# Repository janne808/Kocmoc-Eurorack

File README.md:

# Kocmoc-Eurorack

Copyright (c) 2021 Janne Heikkarainen (janne808@radiofreerobotron.net)

All rights reserved.

### Kocmoc Free Open Source Hardware for Eurorack

* SVF

   Voltage controlled state variable filter design based on the VCV Rack module of the same name. PCB Eurorack compatible panel included.

   Files are made for Eagle 9.x

# Licence

All hardware descriptions, board designs and schematics are released under CERN Open Hardware Licence Version 2 - Strongly Reciprocal, please find the full text as part of this repo

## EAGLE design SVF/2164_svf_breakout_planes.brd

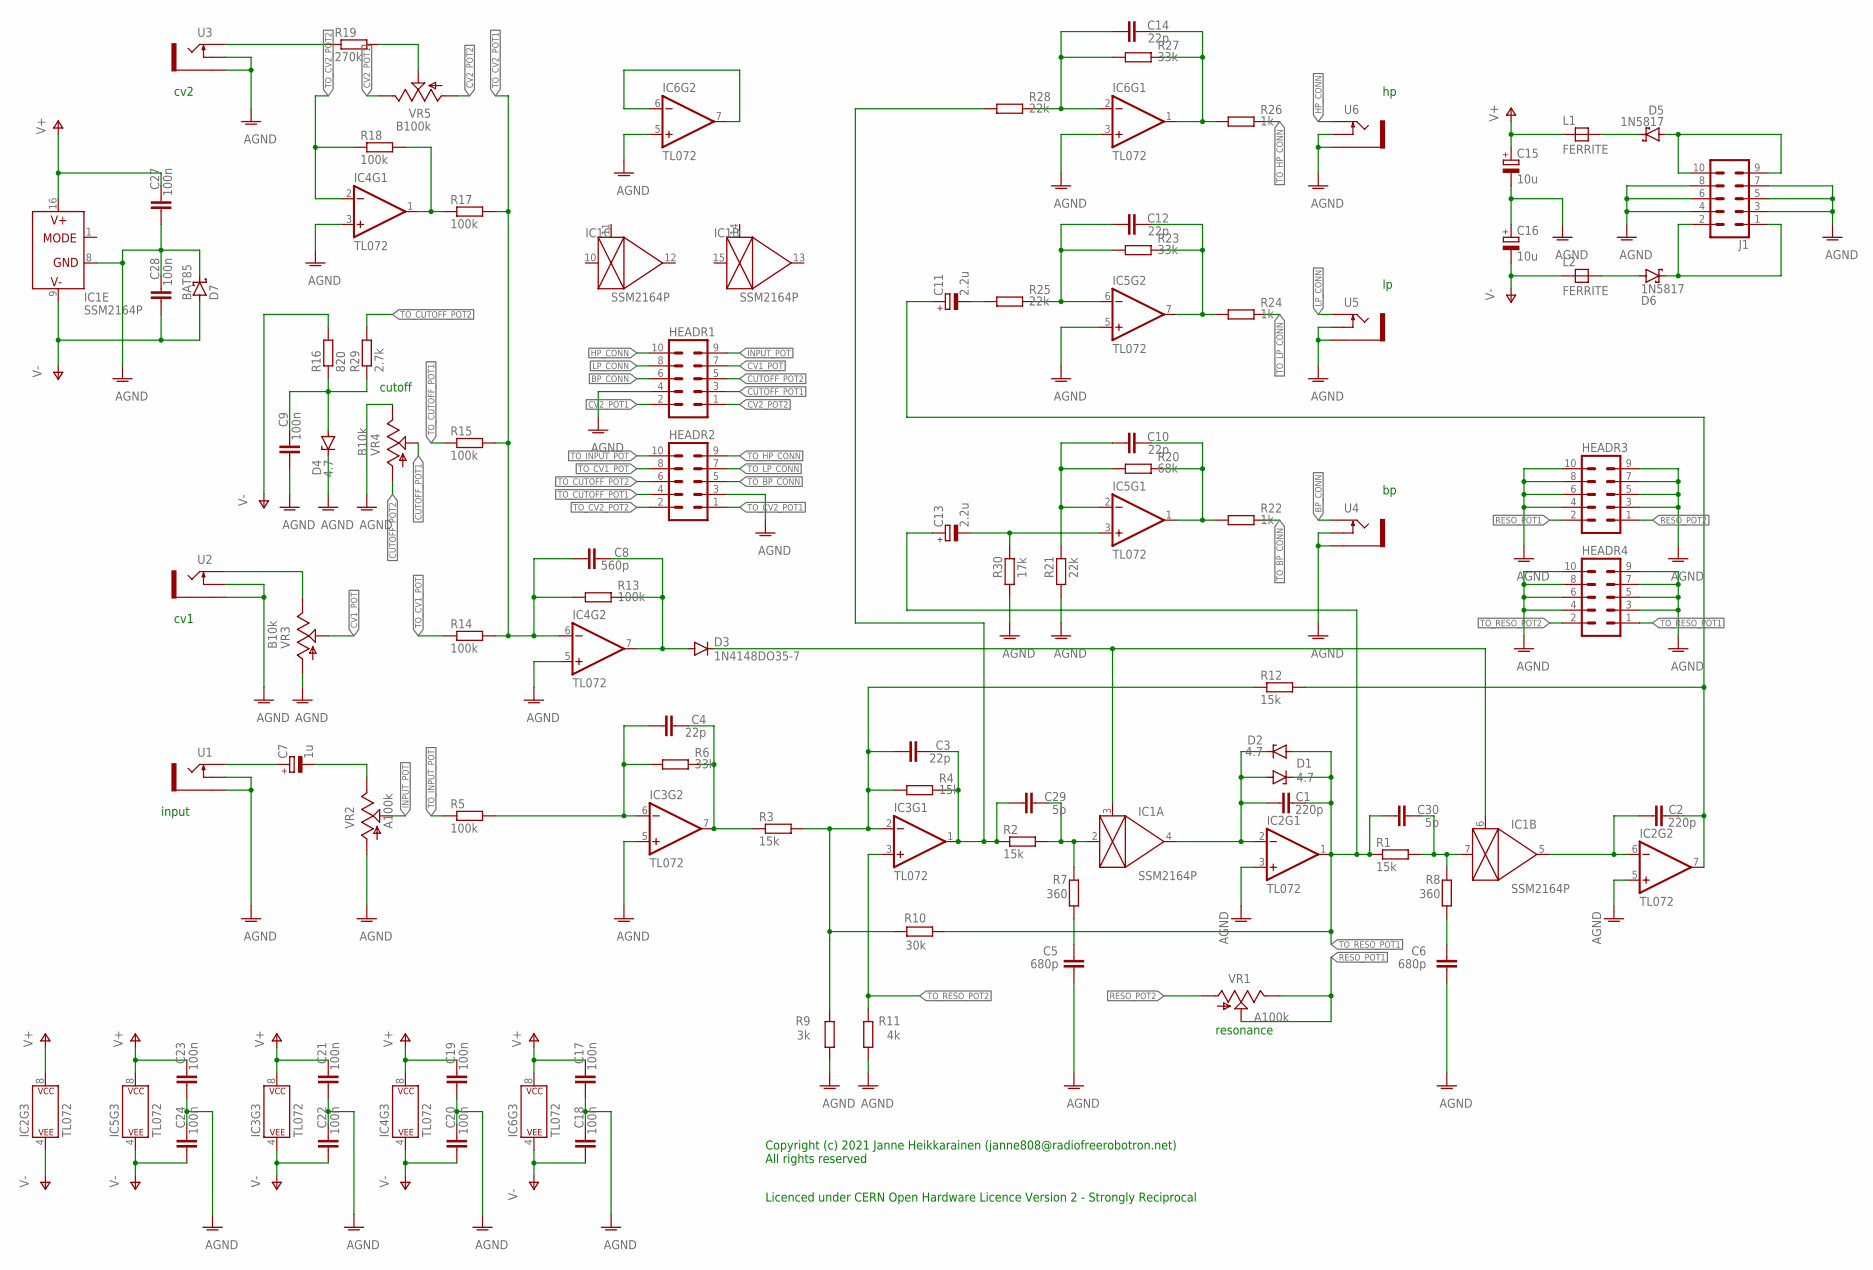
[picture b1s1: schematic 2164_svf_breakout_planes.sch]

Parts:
C1, C2: 220p; C050-025X075
C3, C4, C10, C12, C14: 22p; C050-025X075
C5, C6: 680p; C050-025X075
C7: 1u; E2,5-6E
C8: 560p; C050-025X075
C9, C17, C18, C19, C20, C21, C22, C23, C24, C27, C28: 100n; C050-025X075
C11, C13: 2.2u; E2,5-6E
C15, C16: 10u; E2,5-6E
C29, C30: 5p; C050-025X075
D1, D2, D4: 4.7; DO34Z7
D3: 1N4148DO35-7; DO35-7
D5, D6: 1N5817; DO35-7
D7: BAT85; DO35-7
HEADR1, HEADR2, HEADR3, HEADR4: 10PIN_BACKSIDE
IC1: SSM2164P; DIL16
IC2, IC3, IC4, IC5, IC6: TL072; DIP08
J1: CONN_05X2SHD; 2X5-SHROUDED
L1, L2: FERRITE; FB-085
R1, R2, R3, R4, R12: 15k; 0207/2V
R5, R13, R14, R15, R17, R18: 100k; 0207/2V
R6, R23, R27: 33k; 0207/2V
R7, R8: 360; 0207/2V
R9: 3k; 0207/2V
R10: 30k; 0207/2V
R11: 4k; 0207/2V
R16: 820; 0207/2V
R19: 270k; 0207/2V
R20: 68k; 0207/2V
R21, R25, R28: 22k; 0207/2V
R22, R24, R26: 1k; 0207/2V
R29: 2.7k; 0207/2V
R30: 17k; 0207/2V
U1, U2, U3, U4, U5, U6: THONKICONNNEW; WQP-PJ301M-12_JACK
VR1, VR2: A100k; 9MM_SNAP-IN_POT
VR3, VR4: B10k; 9MM_SNAP-IN_POT
VR5: B100k; 9MM_SNAP-IN_POT

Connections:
AGND: C5.1, C6.1, C9.1, C15.-, C16.+, C17.1, C18.2, C19.1, C20.2, C21.1, C22.2, C23.1, C24.2, C27.1, C28.2, D4.C, D7.C, HEADR1.4, HEADR2.3, HEADR3.3, HEADR3.4, HEADR3.5, HEADR3.6, HEADR3.7, HEADR3.8, HEADR3.9, HEADR3.10, HEADR4.3, HEADR4.4, HEADR4.5, HEADR4.6, HEADR4.7, HEADR4.8, HEADR4.9, HEADR4.10, IC1.8 (GND), IC2.3 (+IN), IC2.5 (+IN), IC3.5 (+IN), IC4.3 (+IN), IC4.5 (+IN), IC5.5 (+IN), IC6.3 (+IN), IC6.5 (+IN), J1.3, J1.4, J1.5, J1.6, J1.7, J1.8, R9.1, R11.1, R21.1, R30.1, U1.P$2_SWITCH (SWITCH), U1.P$3_SLEEVE (SLEEVE), U2.P$2_SWITCH (SWITCH), U2.P$3_SLEEVE (SLEEVE), U3.P$2_SWITCH (SWITCH), U3.P$3_SLEEVE (SLEEVE), U4.P$2_SWITCH (SWITCH), U4.P$3_SLEEVE (SLEEVE), U5.P$2_SWITCH (SWITCH), U5.P$3_SLEEVE (SLEEVE), U6.P$2_SWITCH (SWITCH), U6.P$3_SLEEVE (SLEEVE), VR2.1 (A), VR3.1 (A), VR4.3 (E)
BP_CONN: HEADR1.6, U4.P$1_TIP (TIP)
CUTOFF_POT1: HEADR1.3, VR4.2 (S)
CUTOFF_POT2: HEADR1.5, VR4.1 (A)
CV1_POT: HEADR1.7, VR3.2 (S)
CV2_POT1: HEADR1.2, VR5.3 (E)
CV2_POT2: HEADR1.1, VR5.1 (A)
HP_CONN: HEADR1.10, U6.P$1_TIP (TIP)
INPUT_POT: HEADR1.9, VR2.2 (S)
LP_CONN: HEADR1.8, U5.P$1_TIP (TIP)
unnamed: C1.1, D1.A, D2.C, IC1.4 (OUT), IC2.2 (-IN)
unnamed: C2.1, IC1.5 (OUT), IC2.6 (-IN)
unnamed: C13.-, IC5.3 (+IN), R30.2
unnamed: C30.2, IC1.7 (IN), R1.2, R8.2
unnamed: C3.2, C29.1, IC3.1 (OUT), R2.1, R4.2, R28.1
unnamed: C29.2, IC1.2 (IN), R2.2, R7.2
unnamed: C9.2, D4.A, R16.1, R29.1
unnamed: C4.2, IC3.7 (OUT), R3.1, R6.2
unnamed: C3.1, IC3.2 (-IN), R3.2, R4.1, R9.2, R10.2, R12.1
unnamed: C4.1, IC3.6 (-IN), R5.2, R6.1
unnamed: C2.2, C11.+, IC2.7 (OUT), R12.2
unnamed: C7.-, VR2.3 (E)
unnamed: C7.+, U1.P$1_TIP (TIP)
unnamed: C5.2, R7.1
unnamed: C6.2, R8.1
unnamed: C8.2, D3.A, IC4.7 (OUT), R13.2
unnamed: D3.C, IC1.3 (CTRL), IC1.6 (CTRL)
unnamed: U2.P$1_TIP (TIP), VR3.3 (E)
unnamed: IC4.1 (OUT), R17.1, R18.2
unnamed: C10.1, IC5.2 (-IN), R20.1, R21.2
unnamed: R19.1, U3.P$1_TIP (TIP)
unnamed: R19.2, VR5.2 (S)
unnamed: C10.2, IC5.1 (OUT), R20.2, R22.1
unnamed: C12.1, IC5.6 (-IN), R23.1, R25.2
unnamed: C12.2, IC5.7 (OUT), R23.2, R24.1
unnamed: C11.-, R25.1
unnamed: IC6.6 (-IN), IC6.7 (OUT)
unnamed: D5.C, L1.2
unnamed: C14.2, IC6.1 (OUT), R26.1, R27.2
unnamed: C14.1, IC6.2 (-IN), R27.1, R28.2
unnamed: D6.A, L2.2
unnamed: D6.C, J1.1, J1.2
unnamed: D5.A, J1.9, J1.10
RESO_POT1: HEADR3.2, VR1.2 (S), VR1.3 (E)
RESO_POT2: HEADR3.1, VR1.1 (A)
TO_BP_CONN: HEADR2.5, R22.2
TO_CUTOFF_POT1: HEADR2.4, R15.1
TO_CUTOFF_POT2: HEADR2.6, R29.2
TO_CV1_POT: HEADR2.8, R14.1
TO_CV2_POT1: C8.1, HEADR2.1, IC4.6 (-IN), R13.1, R14.2, R15.2, R17.2
TO_CV2_POT2: HEADR2.2, IC4.2 (-IN), R18.1
TO_HP_CONN: HEADR2.9, R26.2
TO_INPUT_POT: HEADR2.10, R5.1
TO_LP_CONN: HEADR2.7, R24.2
TO_RESO_POT1: C1.2, C13.+, C30.1, D1.C, D2.A, HEADR4.1, IC2.1 (OUT), R1.1, R10.1
TO_RESO_POT2: HEADR4.2, IC3.3 (+IN), R11.2
V+: C15.+, C17.2, C19.2, C21.2, C23.2, C27.2, IC1.16 (V+), IC2.8 (P$V+), IC3.8 (P$V+), IC4.8 (P$V+), IC5.8 (P$V+), IC6.8 (P$V+), L1.1
V-: C16.-, C18.1, C20.1, C22.1, C24.1, C28.1, D7.A, IC1.9 (V-), IC2.4 (P$V-), IC3.4 (P$V-), IC4.4 (P$V-), IC5.4 (P$V-), IC6.4 (P$V-), L2.1, R16.2

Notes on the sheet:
resonance
cutoff
input
cv1
cv2
Copyright (c) 2021 Janne Heikkarainen (janne808@radiofreerobotron.net) All rights reserved
Licenced under CERN Open Hardware Licence Version 2 - Strongly Reciprocal

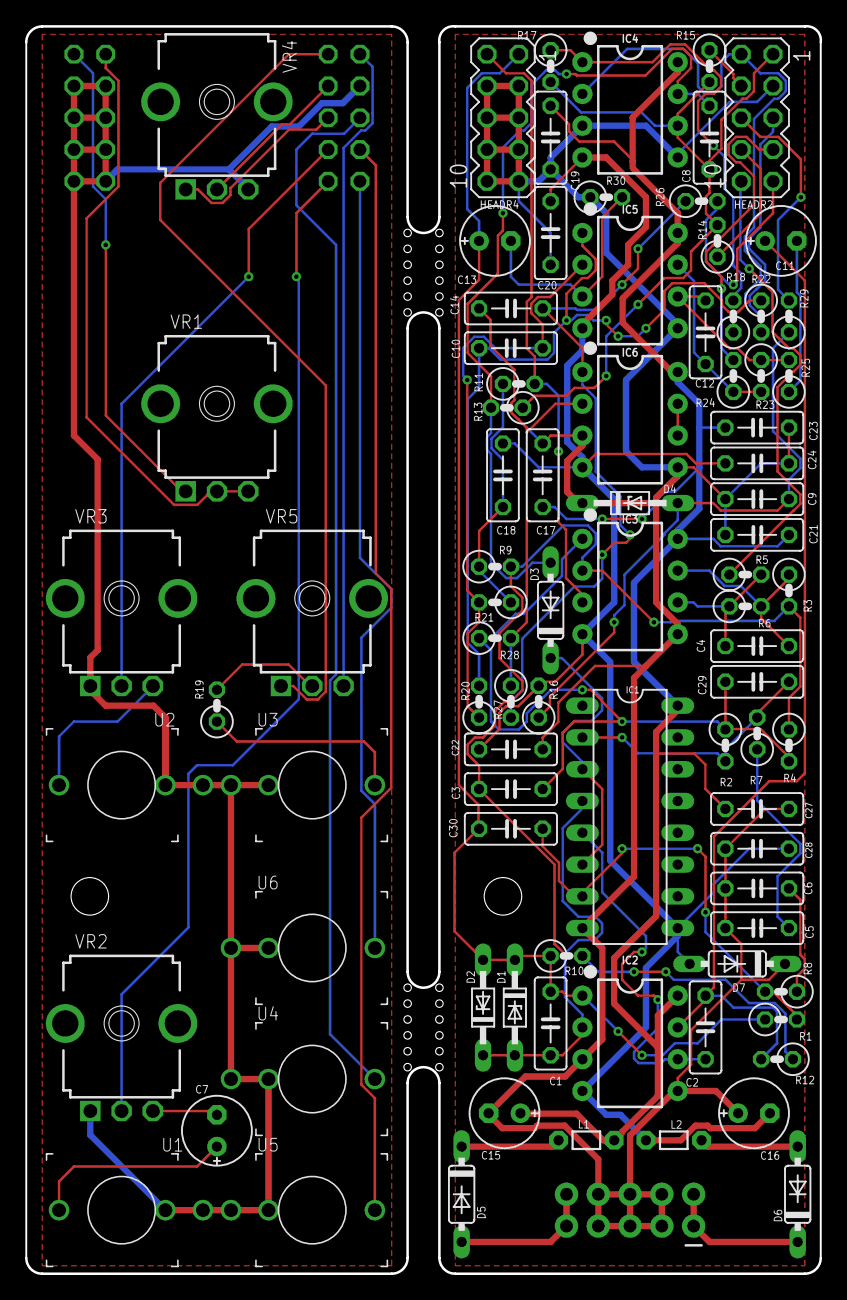
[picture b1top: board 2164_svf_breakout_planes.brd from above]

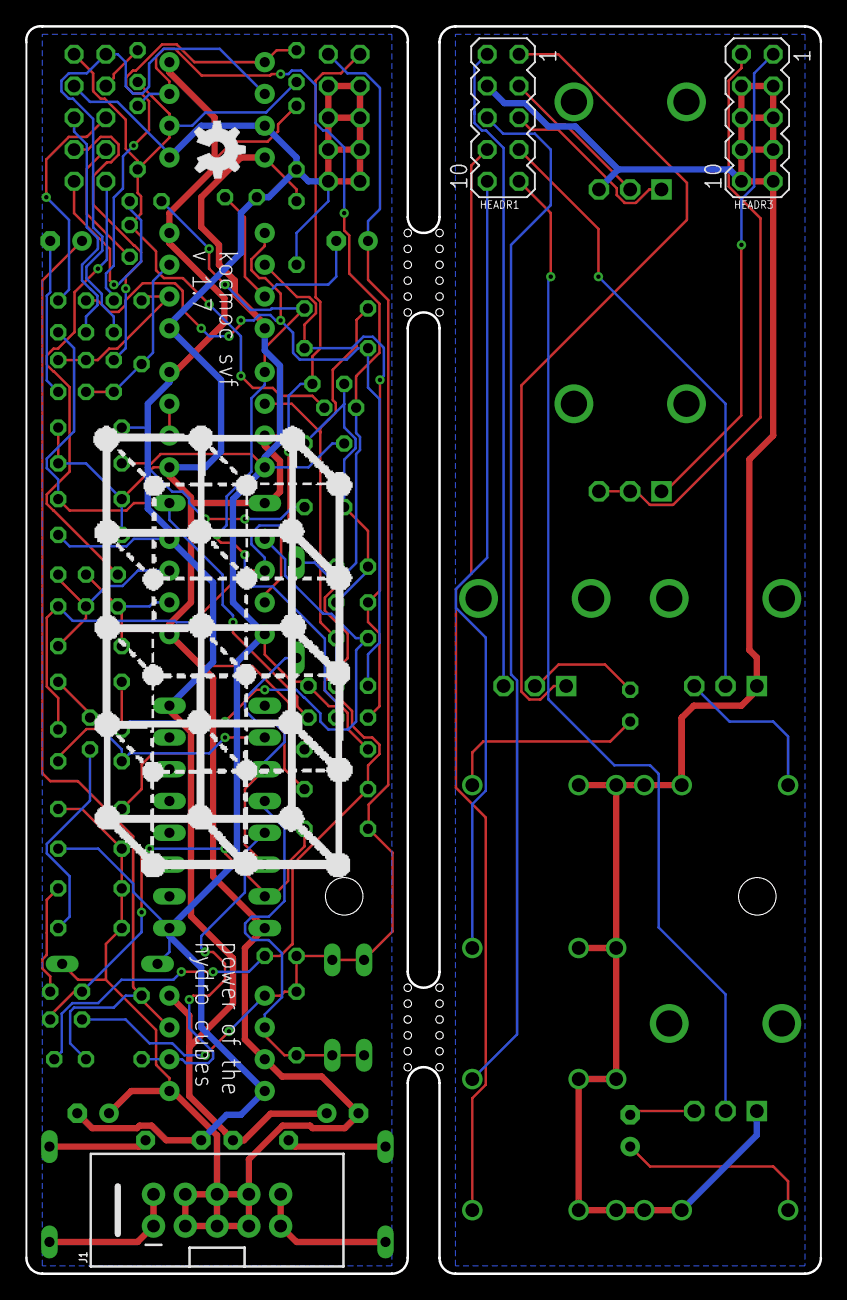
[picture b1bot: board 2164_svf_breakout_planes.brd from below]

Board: 2 copper layers, 63.5 x 99.7 mm, 90 parts (4 on the bottom side), 58 nets.

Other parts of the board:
U$1: OSHW_5MM

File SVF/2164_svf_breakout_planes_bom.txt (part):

Part   Value         Device               Package            Description                                                                                                     MF MPN OC_FARNELL OC_NEWARK POPULARITY PROD_ID    SF_ID     SPICEPREFIX VALUE 
C1     220p          C-EU050-025X075      C050-025X075       CAPACITOR, European symbol                                                                                                                  29                              C                 
C2     220p          C-EU050-025X075      C050-025X075       CAPACITOR, European symbol                                                                                                                  29                              C                 
C3     22p           C-EU050-025X075      C050-025X075       CAPACITOR, European symbol                                                                                                                  29                              C                 
C4     22p           C-EU050-025X075      C050-025X075       CAPACITOR, European symbol                                                                                                                  29                              C                 
C5     680p          C-EU050-025X075      C050-025X075       CAPACITOR, European symbol                                                                                                                  29                              C                 
C6     680p          C-EU050-025X075      C050-025X075       CAPACITOR, European symbol                                                                                                                  29                              C                 
C7     1u            CPOL-EUE2,5-6E       E2,5-6E            POLARIZED CAPACITOR, European symbol                                                                                                        27                              C                 
C8     560p          C-EU050-025X075      C050-025X075       CAPACITOR, European symbol                                                                                                                  29                              C                 
C9     100n          C-EU050-025X075      C050-025X075       CAPACITOR, European symbol                                                                                                                  29                              C                 
C10    22p           C-EU050-025X075      C050-025X075       CAPACITOR, European symbol                                                                                                                  29                              C                 
C11    2.2u          CPOL-EUE2,5-6E       E2,5-6E            POLARIZED CAPACITOR, European symbol                                                                                                        27                              C                 
C12    22p           C-EU050-025X075      C050-025X075       CAPACITOR, European symbol                                                                                                                  29                              C                 
C13    2.2u          CPOL-EUE2,5-6E       E2,5-6E            POLARIZED CAPACITOR, European symbol                                                                                                        27                              C                 
C14    22p           C-EU050-025X075      C050-025X075       CAPACITOR, European symbol                                                                                                                  29                              C                 
C15    10u           CPOL-EUE2,5-6E       E2,5-6E            POLARIZED CAPACITOR, European symbol                                                                                                        27                              C                 
C16    10u           CPOL-EUE2,5-6E       E2,5-6E            POLARIZED CAPACITOR, European symbol                                                                                                        27                              C                 
C17    100n          C-EU050-025X075      C050-025X075       CAPACITOR, European symbol                                                                                                                  29                              C                 
C18    100n          C-EU050-025X075      C050-025X075       CAPACITOR, European symbol                                                                                                                  29                              C                 
C19    100n          C-EU050-025X075      C050-025X075       CAPACITOR, European symbol                                                                                                                  29                              C                 
C20    100n          C-EU050-025X075      C050-025X075       CAPACITOR, European symbol                                                                                                                  29                              C                 
C21    100n          C-EU050-025X075      C050-025X075       CAPACITOR, European symbol                                                                                                                  29                              C                 
C22    100n          C-EU050-025X075      C050-025X075       CAPACITOR, European symbol                                                                                                                  29                              C                 
C23    100n          C-EU050-025X075      C050-025X075       CAPACITOR, European symbol                                                                                                                  29                              C                 
C24    100n          C-EU050-025X075      C050-025X075       CAPACITOR, European symbol                                                                                                                  29                              C                 
C27    100n          C-EU050-025X075      C050-025X075       CAPACITOR, European symbol                                                                                                                  29                              C                 
C28    100n          C-EU050-025X075      C050-025X075       CAPACITOR, European symbol                                                                                                                  29                              C                 
C29    5p            C-EU050-025X075      C050-025X075       CAPACITOR, European symbol                                                                                                                  29                              C                 
C30    5p            C-EU050-025X075      C050-025X075       CAPACITOR, European symbol                                                                                                                  29                              C                 
D1     4.7           ZENER-DIODEDO34-7    DO34Z7             Z-Diode                                                                                                                                     3                                                 
D2     4.7           ZENER-DIODEDO34-7    DO34Z7             Z-Diode                                                                                                                                     3                                                 
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
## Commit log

2021-06-04 Add SVF schematic,board and panel
2021-06-04 Add CERN OHL license text
2021-06-04 Add copyright notice
2021-06-04 Add PDF
2021-06-04 Add BOM
2021-06-16 Add SMD 0603 version of SVF
2021-06-16 Add CHANGES file
2021-06-16 Fine tune README
2021-06-17 Fix backwards footprint graphics for headers and power connector -- note that physical pinouts are unaffected
2021-06-20 Add SVF build instructions
2021-06-27 Update build instructions
2021-07-07 Fix bandpass output AC biasing issue
2021-07-08 Trim output gains for more conservative levels
2021-08-26 Add V1.7 files for SVF
2021-08-27 Minor tweaks for V1.7 build instructions

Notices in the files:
parts and their libraries:
SparkFun-IC-Amplifiers: Licensing: Creative Commons ShareAlike 4.0 International - https://creativecommons.org/licenses/by-sa/4.0
